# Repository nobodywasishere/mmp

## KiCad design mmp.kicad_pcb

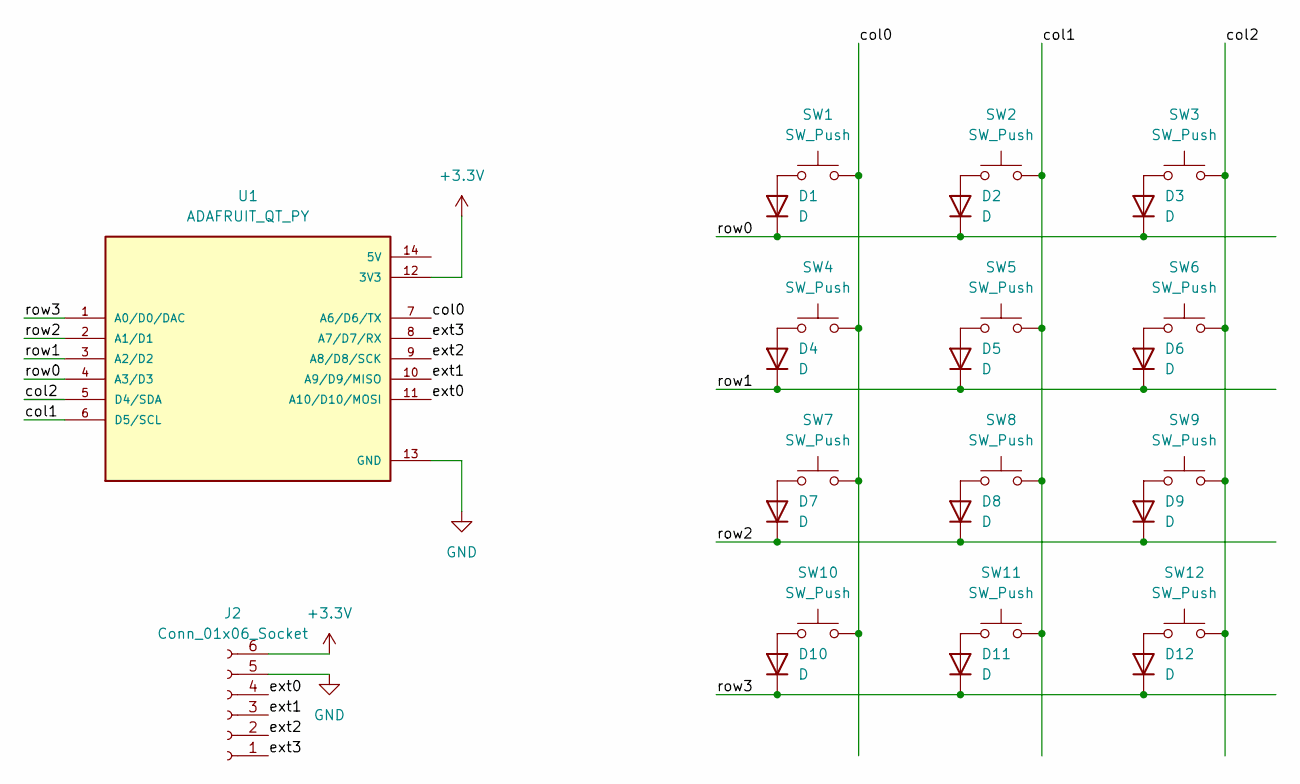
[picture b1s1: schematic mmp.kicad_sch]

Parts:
D1, D2, D3, D4, D5, D6, D7, D8, D9, D10, D11, D12: D; D_1206_3216Metric_Pad1.42x1.75mm_HandSolder
J2: Conn_01x06_Socket; PinHeader_1x06_P2.54mm_Vertical
SW1, SW2, SW3, SW4, SW5, SW6, SW7, SW8, SW9, SW10, SW11, SW12: SW_Push; MX-Solderable-1U
U1: ADAFRUIT_QT_PY; MODULE_ADAFRUIT_QT_PY; PARTREV 2022-12-12

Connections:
+3.3V: J2.6, U1.12 (3V3)
/col0: SW1.2, SW4.2, SW7.2, SW10.2, U1.7 (A6/D6/TX)
/col1: SW2.2, SW5.2, SW8.2, SW11.2, U1.6 (D5/SCL)
/col2: SW3.2, SW6.2, SW9.2, SW12.2, U1.5 (D4/SDA)
/ext0: J2.4, U1.11 (A10/D10/MOSI)
/ext1: J2.3, U1.10 (A9/D9/MISO)
/ext2: J2.2, U1.9 (A8/D8/SCK)
/ext3: J2.1, U1.8 (A7/D7/RX)
/row0: D1.1 (K), D2.1 (K), D3.1 (K), U1.4 (A3/D3)
/row1: D4.1 (K), D5.1 (K), D6.1 (K), U1.3 (A2/D2)
/row2: D7.1 (K), D8.1 (K), D9.1 (K), U1.2 (A1/D1)
/row3: D10.1 (K), D11.1 (K), D12.1 (K), U1.1 (A0/D0/DAC)
GND: J2.5, U1.13 (GND)
unnamed: D1.2 (A), SW1.1
unnamed: D2.2 (A), SW2.1
unnamed: D3.2 (A), SW3.1
unnamed: D4.2 (A), SW4.1
unnamed: D5.2 (A), SW5.1
unnamed: D6.2 (A), SW6.1
unnamed: D7.2 (A), SW7.1
unnamed: D8.2 (A), SW8.1
unnamed: D9.2 (A), SW9.1
unnamed: D10.2 (A), SW10.1
unnamed: D11.2 (A), SW11.1
unnamed: D12.2 (A), SW12.1

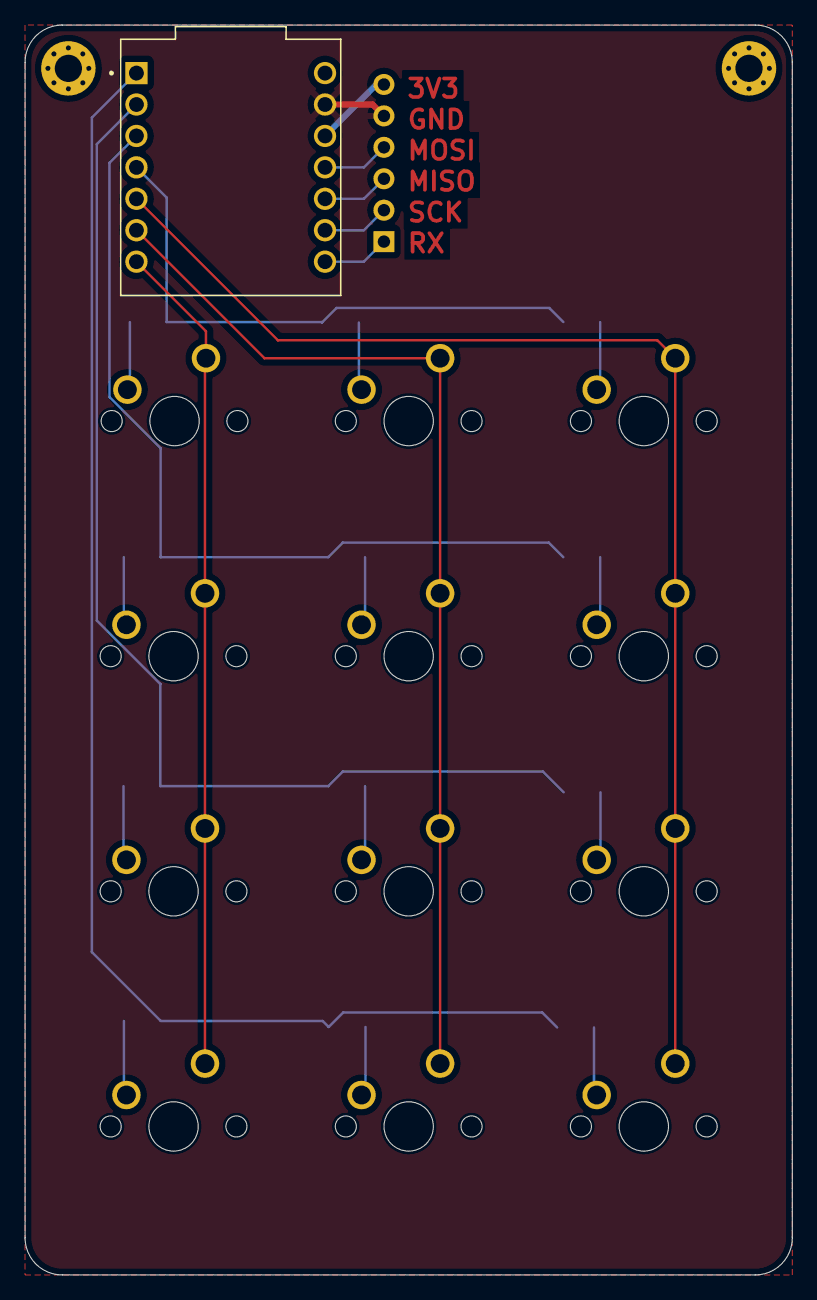
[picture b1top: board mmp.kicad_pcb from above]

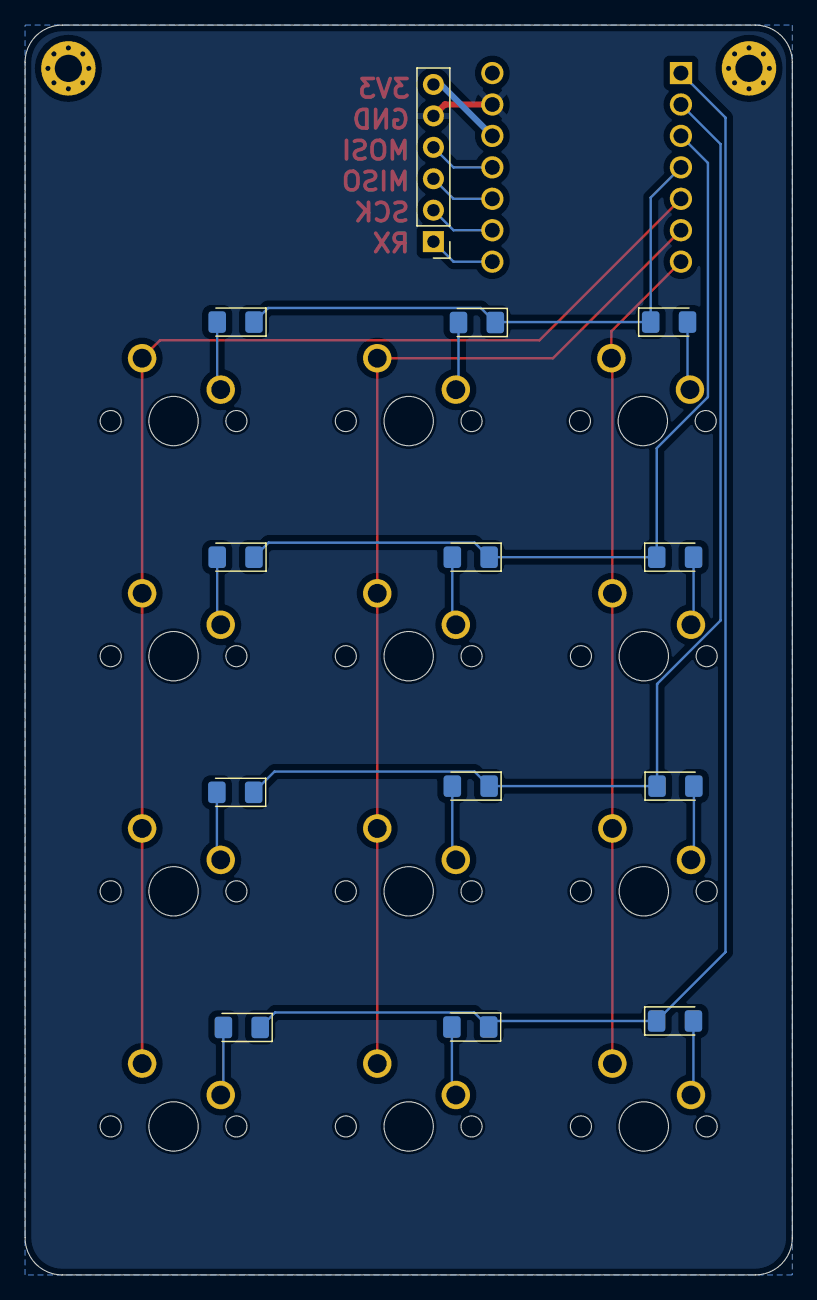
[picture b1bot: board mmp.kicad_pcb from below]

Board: 2 copper layers, 62.0 x 101.0 mm, 26 parts (13 on the bottom side), 25 nets.

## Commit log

2024-03-17 Squashed 'kiswitch/' content from commit 788e851
    git-subtree-dir: kiswitch
    git-subtree-split: 788e851ff22169bffa1dcee89eef2d5653e37102
2024-03-17 Initial pcb layout
2024-03-17 Squashed 'mx_v2/' content from commit 6863a51
    git-subtree-dir: mx_v2
    git-subtree-split: 6863a51f8db475d3d44f44a5df49a99421b1e7d9
2024-03-17 Better pcb layout
2024-03-27 Initial prototype pcb
2024-03-27 stuff
2024-03-27 Squashed 'firmware/' content from commit a1702f5
    git-subtree-dir: firmware
    git-subtree-split: a1702f57f94cdedae1d74128e208ae63948052e2
2024-03-27 Add firmware for mmp
2024-03-27 Move pcb files into pcb folder
2024-03-27 Working MMP firmware
